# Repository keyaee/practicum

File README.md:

T06 - NES LockBox
=========

ECE411 - Practicum project

=======
Remember the Nintendo Entertainment System (NES)? We sure do.  This project is the brain child of Carlos Mariscal.  It simply is a box that locks. But thats not the cool part.  This box is electronically locked, and must be unlocked by using the old school NES controller as a user interface.  

YES! This thing rocks!!!

*[Visit the Wiki!](https://github.com/jalcok1/practicum/wiki)

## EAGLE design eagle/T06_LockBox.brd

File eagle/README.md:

This directory will hold needed Eagle .lib, .sch, and .brd
files necessary for the practicum project

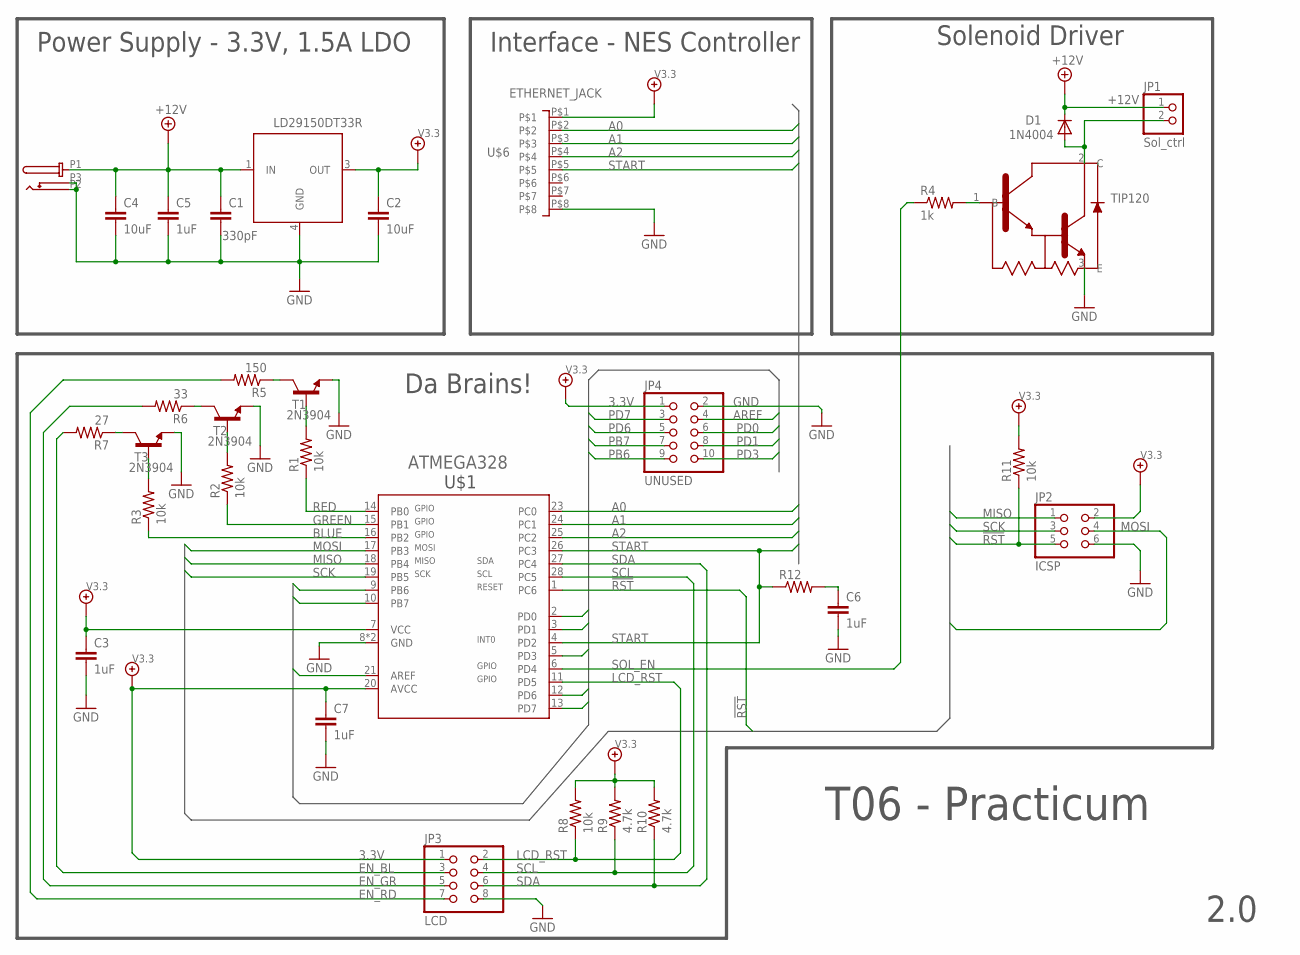
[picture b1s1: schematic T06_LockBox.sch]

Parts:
C1: 330pF; C0805
C2: 10uF; C0805
C3, C5, C6, C7: 1uF; C0805
C4: 10uF; C1206
D1: 1N4004; DO41-10
JP1: Sol_ctrl; 1X02
JP2: ICSP; 2X03
JP3: LCD; 2X04
JP4: UNUSED; 2X05
R1, R2, R3, R8: 10k; R0805
R4: 1k; M0805
R5: 150; R0805
R6: 33; R0805
R7: 27; R0805
R9, R10: 4.7k; R0805
R11: 10k; M0805
R12: R-US_M0805; M0805
T1, T2, T3: 2N3904; TO92-BCE
U$1: ATMEGA328; DIL28-3
U$2: LD29150DT33R; DPAK
U$3: PJ-102A
U$4: TIP120; T0220-3
U$6: ETHERNET_JACK; MODJACK8

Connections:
3.3V: C2.1, C3.1, C7.1, JP2.2, JP3.1, JP4.1, R8.2, R9.2, R10.2, R11.2, U$1.7 (VCC), U$1.20 (AVCC), U$2.3 (OUT), U$6.P$1
!RST: JP2.5, R11.1, U$1.1 (PC6)
+12V: C1.1, C4.1, C5.1, D1.C, JP1.1, U$2.1 (IN), U$3.P1 (PWR)
A0: U$1.23 (PC0), U$6.P$2
A1: U$1.24 (PC1), U$6.P$3
A2: U$1.25 (PC2), U$6.P$4
AREF: JP4.4, U$1.21 (AREF)
BLUE: R3.1, U$1.16 (PB2)
EN_BL: JP3.3, R7.2
EN_GR: JP3.5, R6.2
EN_RD: JP3.7, R5.2
GND: C1.2, C2.2, C3.2, C4.2, C5.2, C6.2, C7.2, JP2.6, JP3.8, JP4.2, T1.E, T2.E, T3.E, U$1.8 (GND), U$1.22 (GND), U$2.4 (GND), U$3.P2 (GND), U$3.P3 (GND), U$4.3 (E), U$6.P$8
GREEN: R2.1, U$1.15 (PB1)
LCD_RST: JP3.2, R8.1, U$1.11 (PD5)
MISO: JP2.1, U$1.18 (PB4)
MOSI: JP2.4, U$1.17 (PB3)
unnamed: R4.2, U$4.1 (B)
unnamed: C6.1, R12.2
unnamed: D1.A, JP1.2, U$4.2 (C)
unnamed: R1.2, T1.B
unnamed: R2.2, T2.B
unnamed: R3.2, T3.B
unnamed: R7.1, T3.C
unnamed: R6.1, T2.C
unnamed: R5.1, T1.C
PB6: JP4.9, U$1.9 (PB6)
PB7: JP4.7, U$1.10 (PB7)
PD0: JP4.6, U$1.2 (PD0)
PD1: JP4.8, U$1.3 (PD1)
PD3: JP4.10, U$1.5 (PD3)
PD6: JP4.5, U$1.12 (PD6)
PD7: JP4.3, U$1.13 (PD7)
RED: R1.1, U$1.14 (PB0)
SCK: JP2.3, U$1.19 (PB5)
SCL: JP3.4, R9.1, U$1.28 (PC5)
SDA: JP3.6, R10.1, U$1.27 (PC4)
SOL_EN: R4.1, U$1.6 (PD4)
START: R12.1, U$1.4 (PD2), U$1.26 (PC3), U$6.P$5

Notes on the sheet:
Power Supply - 3.3V, 1.5A LDO
Interface - NES Controller
Solenoid Driver
T06 - Practicum
2.0
Da Brains!

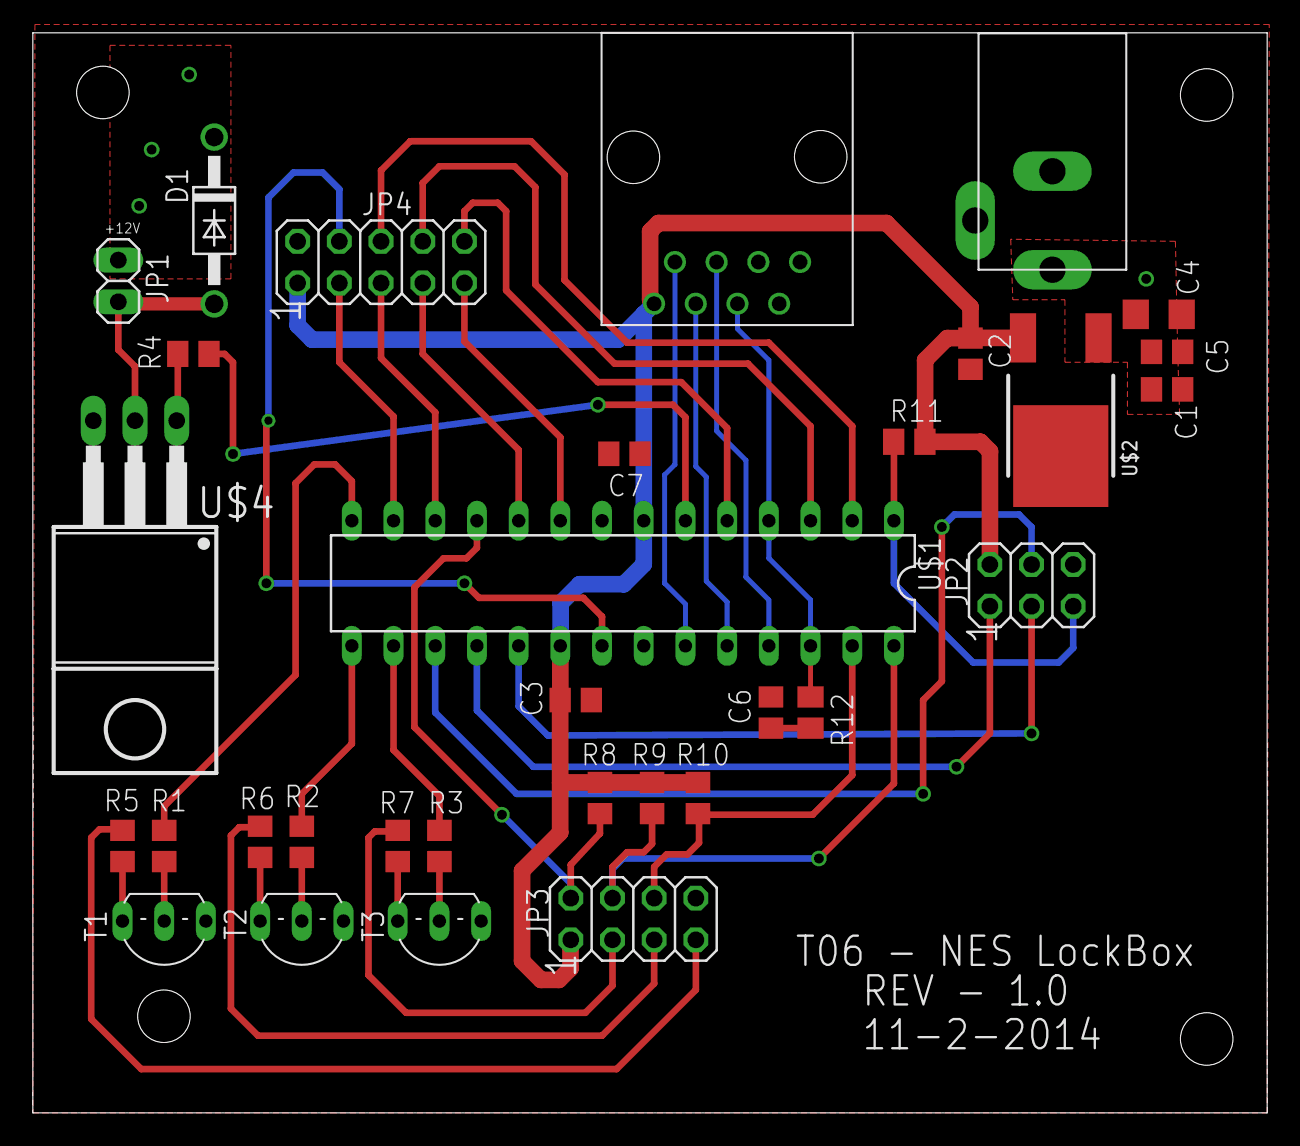
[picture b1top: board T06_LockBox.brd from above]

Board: 2 copper layers, 75.2 x 65.8 mm, 32 parts (0 on the bottom side), 38 nets.

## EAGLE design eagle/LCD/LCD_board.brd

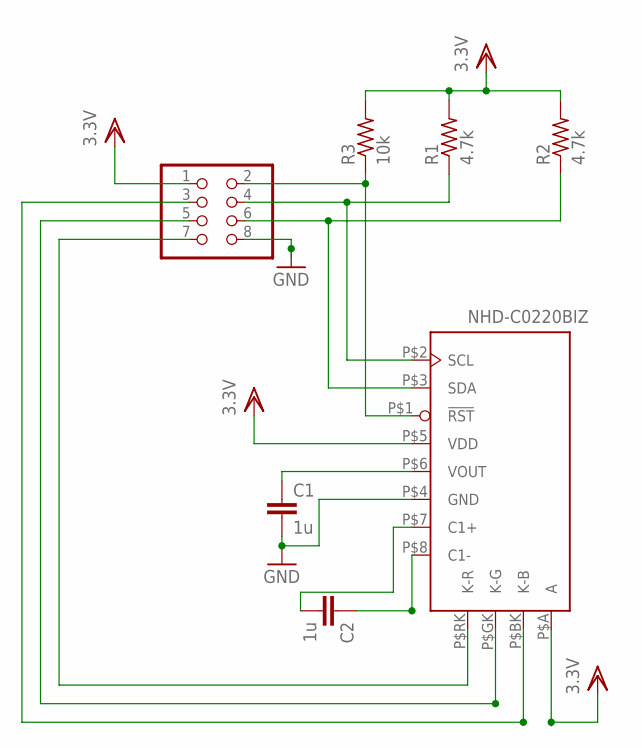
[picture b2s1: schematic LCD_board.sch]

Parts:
C1, C2: 1u; C0805
DATALINES: To MPU; 2X04
R1, R2: 4.7k; M0805
R3: 10k; M0805
U$1: NHD-C0220BIZ; NHD-C0220BIZ-LCD

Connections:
3.3V: DATALINES.1, R1.2, R2.2, R3.2, U$1.P$5 (VDD), U$1.P$A (A)
!LCD_RST: DATALINES.2, R3.1, U$1.P$1 (!RST)
C1+: C2.2, U$1.P$7 (C1+)
EN_BL: DATALINES.3, U$1.P$BK (K-B)
EN_G: DATALINES.5, U$1.P$GK (K-G)
EN_RD: DATALINES.7, U$1.P$RK (K-R)
GND: C1.2, DATALINES.8, U$1.P$4 (GND)
unnamed: C2.1, U$1.P$8 (C1-)
unnamed: C1.1, U$1.P$6 (VOUT)
SCL: DATALINES.4, R1.1, U$1.P$2 (SCL)
SDA: DATALINES.6, R2.1, U$1.P$3 (SDA)

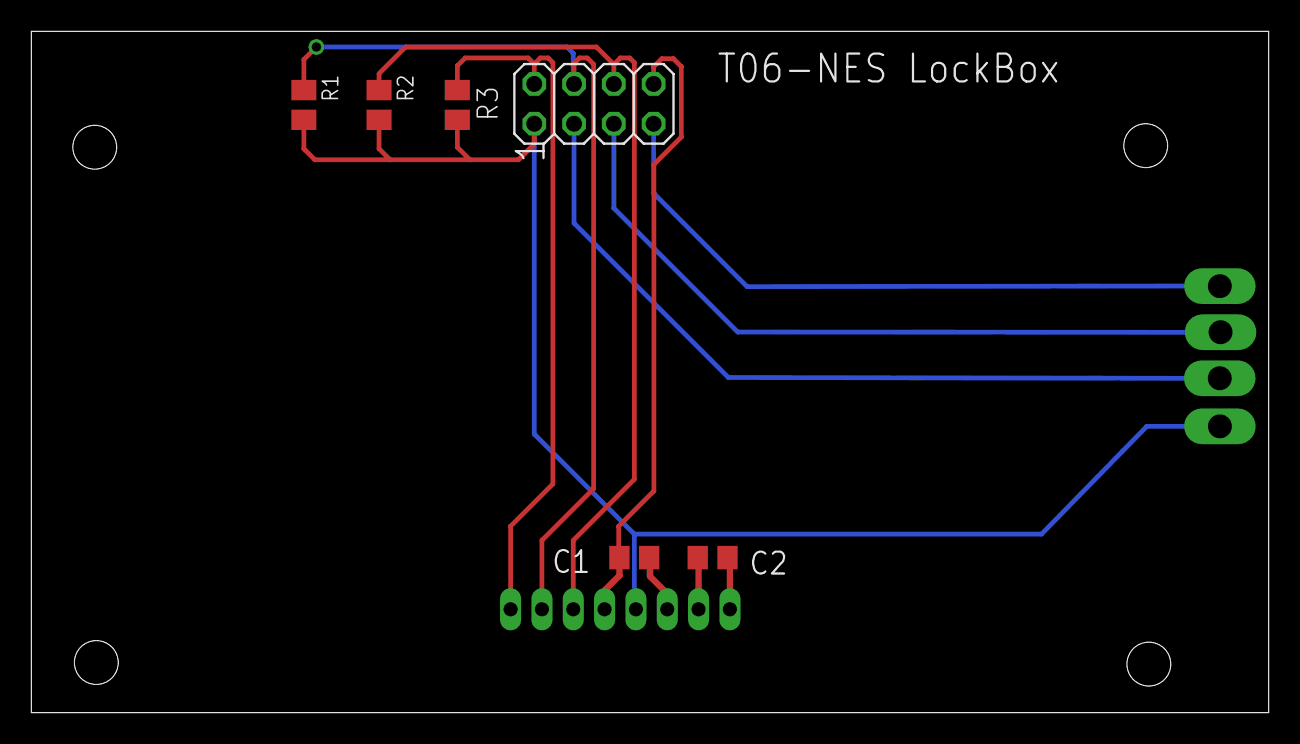
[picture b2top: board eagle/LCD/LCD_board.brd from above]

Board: 2 copper layers, 79.0 x 43.5 mm, 7 parts (1 on the bottom side), 11 nets.

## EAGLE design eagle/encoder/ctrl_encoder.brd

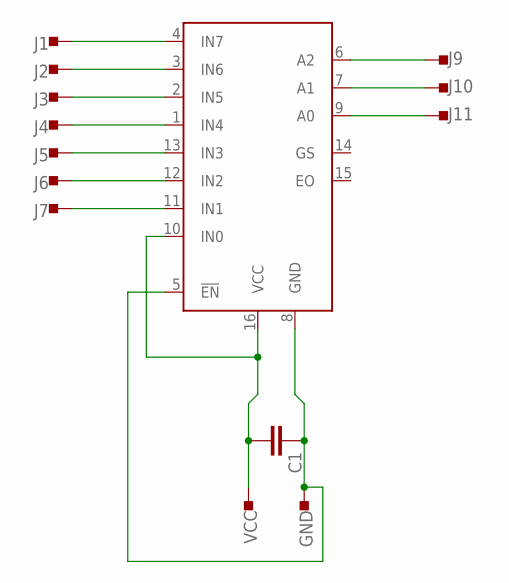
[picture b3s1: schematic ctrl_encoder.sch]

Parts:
C1: C; C0805
GND: PAD; TEST_PAD
J1, J2, J3, J4, J5, J6, J7, J9, J10, J11: PAD; TEST_PAD
U$1: SN74HC148DR; SO16
VCC: PAD; TEST_PAD

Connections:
GND: C1.1, GND.P$1, U$1.5 (!EN), U$1.8 (GND)
unnamed: C1.2, U$1.10 (IN0), U$1.16 (VCC), VCC.P$1
unnamed: J9.P$1, U$1.6 (A2)
unnamed: J1.P$1, U$1.4 (IN7)
unnamed: J2.P$1, U$1.3 (IN6)
unnamed: J3.P$1, U$1.2 (IN5)
unnamed: J4.P$1, U$1.1 (IN4)
unnamed: J5.P$1, U$1.13 (IN3)
unnamed: J6.P$1, U$1.12 (IN2)
unnamed: J7.P$1, U$1.11 (IN1)
unnamed: J10.P$1, U$1.7 (A1)
unnamed: J11.P$1, U$1.9 (A0)

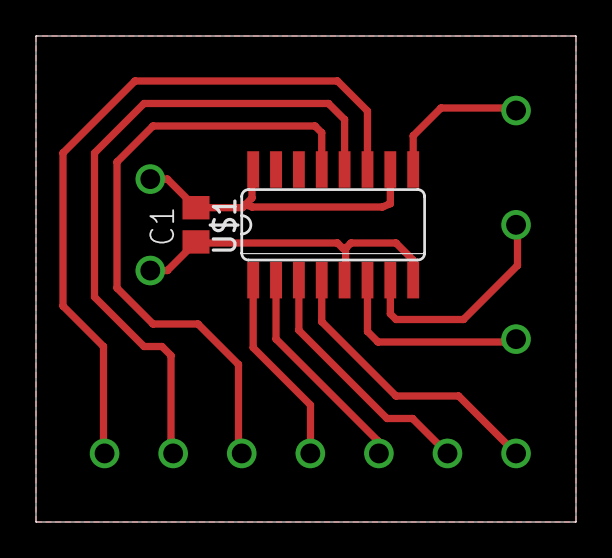
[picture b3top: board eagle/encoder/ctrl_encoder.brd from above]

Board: 2 copper layers, 30.0 x 27.0 mm, 14 parts (0 on the bottom side), 12 nets.

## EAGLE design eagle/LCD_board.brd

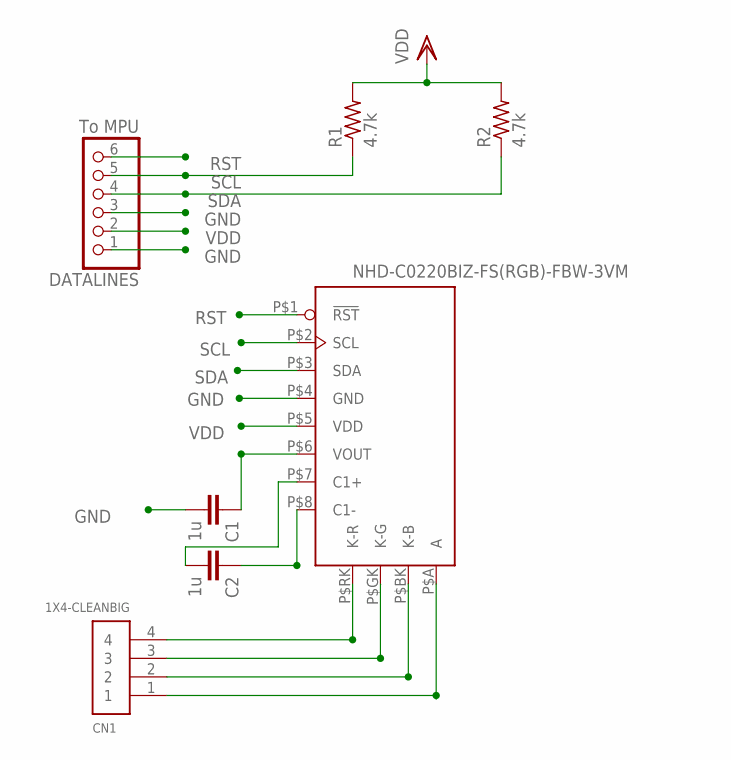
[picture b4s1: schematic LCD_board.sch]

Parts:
C1, C2: 1u; C15B8
CN1: 1X4-CLEANBIG; 1X04-CLEANBIG
DATALINES: To MPU; 1X06
R1, R2: 4.7k; 0204/5
U$1: NHD-C0220BIZ-FS(RGB)-FBW-3VM; NHD-C0220BIZ-LCD

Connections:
A: CN1.4, U$1.P$RK (K-R)
C1+: C2.2, U$1.P$7 (C1+)
GK: CN1.2, U$1.P$BK (K-B)
GND: C1.2, DATALINES.1, DATALINES.3, U$1.P$4 (GND)
unnamed: C2.1, U$1.P$8 (C1-)
unnamed: CN1.3, U$1.P$GK (K-G)
unnamed: C1.1, U$1.P$6 (VOUT)
unnamed: CN1.1, U$1.P$A (A)
RST: DATALINES.6, U$1.P$1 (!RST)
SCL: DATALINES.5, R1.1, U$1.P$2 (SCL)
SDA: DATALINES.4, R2.1, U$1.P$3 (SDA)
VDD: DATALINES.2, R1.2, R2.2, U$1.P$5 (VDD)

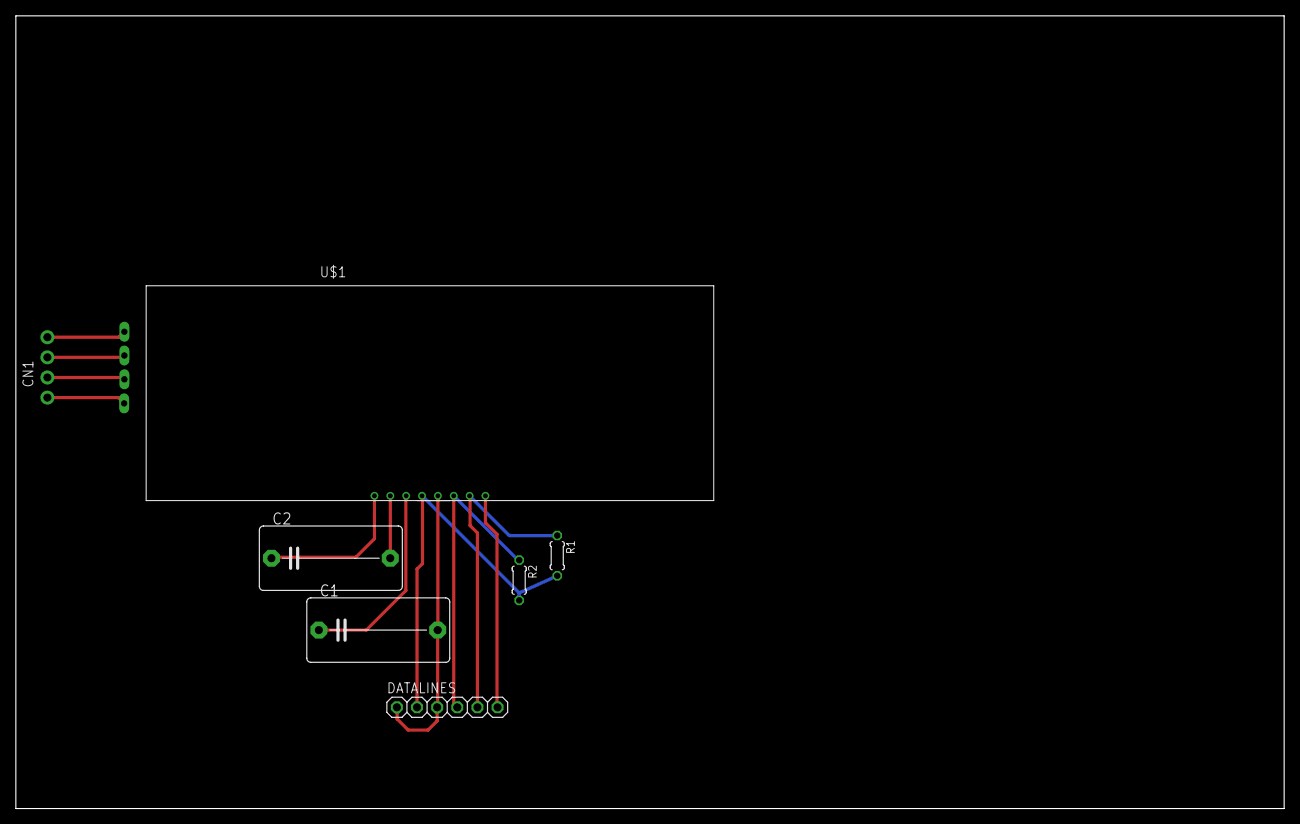
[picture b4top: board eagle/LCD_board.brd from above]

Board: 2 copper layers, 160.0 x 100.0 mm, 7 parts (0 on the bottom side), 12 nets.

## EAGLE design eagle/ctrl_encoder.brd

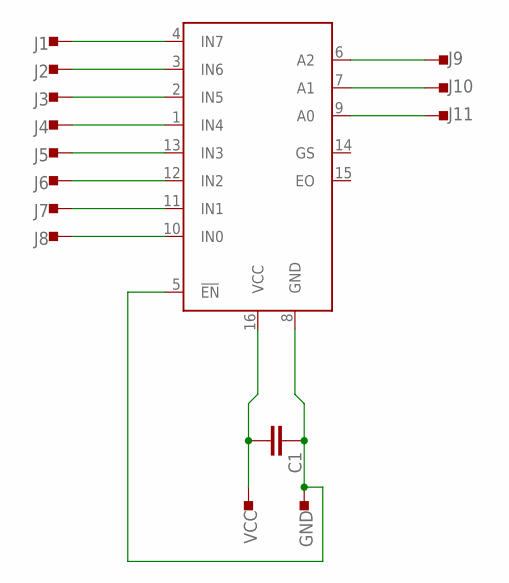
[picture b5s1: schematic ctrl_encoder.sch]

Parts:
C1: C; C0805
GND: PAD+SQUARE-1.5X1.5; PAD-1.5X1.5
J1, J2, J3, J4, J5, J6, J7, J8, J9, J10, J11: PAD+SQUARE-1.5X1.5; PAD-1.5X1.5
U$1: SN74HC148DR; SO16
VCC: PAD+SQUARE-1.5X1.5; PAD-1.5X1.5

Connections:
GND: C1.1, GND.PAD, U$1.5 (!EN), U$1.8 (GND)
unnamed: C1.2, U$1.16 (VCC), VCC.PAD
unnamed: J9.PAD, U$1.6 (A2)
unnamed: J1.PAD, U$1.4 (IN7)
unnamed: J2.PAD, U$1.3 (IN6)
unnamed: J3.PAD, U$1.2 (IN5)
unnamed: J4.PAD, U$1.1 (IN4)
unnamed: J5.PAD, U$1.13 (IN3)
unnamed: J6.PAD, U$1.12 (IN2)
unnamed: J7.PAD, U$1.11 (IN1)
unnamed: J8.PAD, U$1.10 (IN0)
unnamed: J10.PAD, U$1.7 (A1)
unnamed: J11.PAD, U$1.9 (A0)

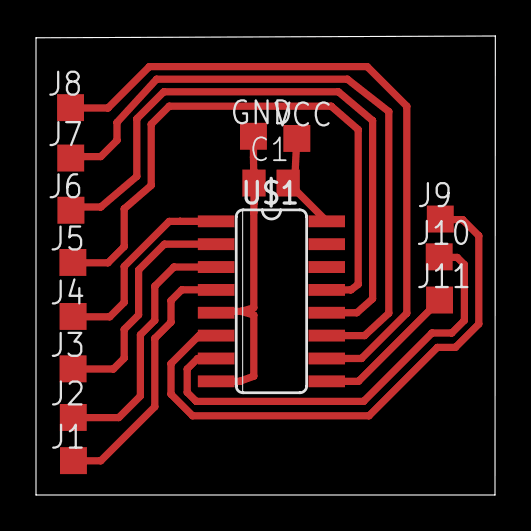
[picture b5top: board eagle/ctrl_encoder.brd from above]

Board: 2 copper layers, 25.5 x 25.5 mm, 15 parts (0 on the bottom side), 13 nets.

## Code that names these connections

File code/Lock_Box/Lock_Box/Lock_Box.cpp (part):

/*
this code is used to debug the NES controller interface,external interrupts, and timer interrupts.
LEDs are used for debug and are placed on pin B0-B3 with some resistors in series ~1kohm.
the input pins from the encoder are PC0-PC3 

I have started to write the main loop for the lock box I have incorporated the code that i had and have left 
to do comments through out the code. 
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an interrupt described above*/
ISR(TIMER1_COMPA_vect)
{
	//for debug-toggle LED on PB4++++++++++++++++++++++++++++++++++++++++++
	PORTB |= (1<<PORTB4); //turn blue LED on to signify we are in at home screen
	PORTB &= ~(1<<PORTB3); //turn red LED off
	//++++++++++++++++++++++++++++++++++++++++++
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
int main(void)
{
    //setting PBC0-PC3 as inputs
	DDRC &= ~((1<<DDC0)|(1<<DDC1)|(1<<DDC2)|(1<<DDC3));//all port B as inputs
	PORTC |= ((1<<PORTC0)|(1<<PORTC1)|(1<<PORTC2)|(1<<PORTC3));//enable pull-ups

	
	DDRB |= ((1<<DDB0)|(1<<DDB1)|(1<<DDB2)|(1<<DDB3)|(1<<DDB4)|(1<<DDB5)|(1<<DDB6)); //pin PB0-PB3 as outputs
	PORTB = 0x00;// all off
	 
	
	//configuring interrupt INT0
	DDRD &= ~(1<<DDD2); //PD2 as input
	PORTD |= (1<<PORTD2); //enable pull-up on PD2
	EICRA |= (1<<ISC01); //set interrupt on INT0 falling edge
	EIMSK |= (1<<INT0); //enable interrupt on INT0
	
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
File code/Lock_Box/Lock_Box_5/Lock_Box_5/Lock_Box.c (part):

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
int main(void)
{
    //setting PBC0-PC3 as inputs
	DDRC &= ~((1<<DDC0)|(1<<DDC1)|(1<<DDC2)|(1<<DDC3));//all port B as inputs
	PORTC |= ((1<<PORTC0)|(1<<PORTC1)|(1<<PORTC2)|(1<<PORTC3));//enable pull-ups
	
	DDRD |= ((1<<DDD5)|(1<<DDD4)); // setting PD5 and PD4 as output for solenoid and reset for LCD
	PORTD |= (1<<PORTD4); //set high for LCD reset (reset is active low)
	
	DDRB |= ((1<<DDB0)|(1<<DDB1)|(1<<DDB2)); //PB0-PB2 as outputs for LCD LEDs control
	
	LEDs(1,1,1); //all on -white

	
	
	//configuring interrupt INT0
	DDRD &= ~(1<<DDD2); //PD2 as input
	PORTD |= (1<<PORTD2); //enable pull-up on PD2
	EICRA |= (1<<ISC01); //set interrupt on INT0 falling edge
	EIMSK |= (1<<INT0); //enable interrupt on INT0
	
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
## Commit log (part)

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2014-10-02 Added eagle directory to the repo, this will hold all eagle associated files for the practicum project.
2014-10-02 Adding a datasheet directory
2014-10-03 This is to practice committing and syncing
2014-10-08 test changes
2014-10-08 Removing test changes to README.md
2014-10-08 testing app commit
    testing app commit
2014-10-08 atmega 328p data sheet
2014-10-08 adding parts with data sheets and supporting files
2014-10-08 block diagram of project
2014-10-08 moved the Atmel datasheet from datasheets directory to the parts/MCU directory to be consistant with the file system
2014-10-08 renamed spaces from block diagram jpg
2014-10-08 Added the controller interface jpeg to the ControllerMCUinterface.docx and modified naming conventions.
2014-10-08 new schematic for controller
2014-10-08 Testing commit for Luis
    added line to REDME.md
2014-10-09 adding some data sheets
2014-10-09 updates and adding a folder for invoices
2014-10-09 Started LockBox.lbr and added the ATMEGA328 symbol/footprint
2014-10-09 Minor formatting and puncuation changes.
2014-10-09 updating block diagram
2014-10-09 last project
    added the last project idea
2014-10-10 deleting copy
2014-10-10 Added LCD screen footprint and schematic to library
2014-10-11 adding some schematics and data sheets
2014-10-11 datasheets to datasheets folder
2014-10-11 naming files appropriately
2014-10-11 Small changes
2014-10-11 Added LDO schematic and footprint to LockBox.lbr
2014-10-11 Carlos data sheet mistake change
2014-10-11 deleting incorrect datasheets
2014-10-11 Added TIP120 Darlington Transistor footprint and schematic to Lockbox.lbr
2014-10-11 LCD board
    Jeff, I do have some issues
2014-10-12 Added S016 package to the 8:3 encoder
2014-10-12 Created footprint for the DC power jack
2014-10-12 Added symbol for the DC power jack to the LockBox.lbr
2014-10-12 Arduino pin out vs. atmega328
2014-10-12 cleaning up atmega328 folder
2014-10-13 Updating files
2014-10-13 Added names, changed presentation
2014-10-13 Deleted duplicate LCD_board.b#d and LCD_board.brd from eagle directory. Created a new LCD_board.brd file that no longer causes errors when trying to open it via eagle
2014-10-13 removed duplicate LCD_board.b#1 file from the repo
2014-10-13 DRC errors in the LCD_board.brd have been resolved. Traces have been routed and the board should be good to go.
2014-10-13 ethernet jack
    here u go jefe
2014-10-14 correction
2014-10-14 adding pinout
2014-10-16 created ctrl encoder board and schematic.
2014-10-16 minor change
2014-10-16 LCD board with pull up resistor
    This should give us a working screen with thru hole components just to
    check dimensions and use for debug. Next change resistor and capacitor
    for surface mount and determine if RGB resistors will be on this or the
    main board.
2014-10-16 Added gerber files folders
    The name are a redundant since the extension tells you what they are
    but I thought it was the easiest way for everybody to understand
2014-10-16 Added schematic frame to the library
2014-10-16 LCD Gerber files
    PSU formated Gerber files for LPKF
2014-10-17 Moved ctrl_encoder.dri file to GerberFiles/encoder Renamed Gerber\ files to GerberFiles
2014-10-17 More file management, added LCD folder and encoder folder and moved appropiate files.
2014-10-17 moved j1-j8 pins up on the ctrl_encoder.brd shrinking the actual size of the encoder board by several mm.
2014-10-18 blah blka
2014-10-18 controller driver
2014-10-18 updates
    added comments and some new variables.
2014-10-19 uptades
    added invoice for eBay
2014-10-19 invoice for ebay
2014-10-20 updates
    updated controller schematic
    added basic program flow
    updated pin out to MCU and encoder
2014-10-20 Added ground symbol to LockBox.lbr
2014-10-20 Modified the ATMEL chip schematic in LockBox.lbr, the schematic now updates properly when adding attributes to the port/pins in LockBox.sch.
2014-10-20 Finished the powersupply and LDO portion of the LockBox.sch, Added pwr/gnd and bypass cap to the ATMEL chip, updateded I2C pin attributes and added I2C bus.
2014-10-20 Added gnd and vout connections to the LCD screen in LockBox.sch Moved pins and modified part name in LockBox.lbr. These pins were poorly placed and were moved to allow for a cleaner schematic in Lock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
2014-10-20 Added KR, KG, KB, and A connections to the LCD screen.
2014-10-20 Updated LCD_board.sch with modified LCD screen schematic.
2014-10-20 LCD_board.brd is now a one layer board. Created new Gerber files and updated the GerberFiles/LCD directory with these new files
2014-10-20 updated ATMEL chip pin allocation.
2014-10-21 created folder for 411 class assignments
    we can put class assignments stuffs here
2014-10-21 Delete Microcontroller Tutorial - A Beginners Guide - YouTube.webloc
    will add a text file with link to youtube videos
2014-10-21 link to useful AVR tutorial
2014-10-21 Modified the symbol on the TIP120. The grid of the schematic was on an off scale making it difficult to make wire connections when using the part in the LockBox.sch.
2014-10-21 Added 0.6mm drill Test pad to LockBox.lbr
2014-10-21 Replaced surface mount pads with through hole pads. Added a polygon to the .brd and increased the size of the isolate from 10mil to 20mils, this should prevent solder from bridging to the remaining c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
2014-10-21 Removed previous gerber files and added new updated gerber files
2014-10-21 Ver2 Gerber files for encoder
    Per Carlos request created new Gerber files for encoder with thru hole.
2014-10-21 updates
    added some more bullet points
2014-10-21 program flow change
    SELECT button will cause interrupt only in first screen
2014-10-21 updating pin out
2014-10-21 datasheet for diode in parallel with solenoid
2014-10-21 Added 2pin header and 12V supply symbol to LockBox.lbr
2014-10-21 changed pin out
    had to change the pinout of the MCU because the outputs of the
    Controller are pull ups and one of the pins I was using was the same
    for the SPI bus which need to be free not pulled high or else
    programming would not be possible
2014-10-21 Added bus and related nets for LED color control on the LCD screen
2014-10-22 changes on pinout
2014-10-22 adding new Driver for controller
    this code contains an update for the controller driver and also
    includes examples on external interrupts and timer interrupts
2014-10-22 Increased the size of the test pad through hole from 0.6mm to 1.1mm
2014-10-22 Testing Keya's git push pull
2014-10-23 Added cool info the the REDME.md file. The info in this file is the first thing that is visable when opening our GITHUB home page.
2014-10-23 removed the README.md
2014-10-24 Lock Box code
    the code is mostly done. we only need to develop drivers for the LCD. I
    tried to comment most of the code I will continue to add comments ASAP.
2014-10-24 adding folder for images and videos
    we can use this folder to document our progress with images
2014-10-24 testing for size
2014-10-24 testing size
2014-10-24 updating images
2014-10-24 Update to assignment 3 document
2014-10-24 Others will need to contribute to this document
2014-10-25 edit to PDS
    IU made some edits to the PDS
2014-10-25 no changes...
    just my MAC being crazy
2014-10-25 Added team number to title page, added information for the cost and environmental categories, also made some small formatting changes.
2014-10-25 small edits
    did some editing on the document
2014-10-25 File management: I cleaned up the practicum directory
2014-10-25 Minor changes and suggestions
    Used track changes and comments to identify my ideas and make it easy
    to accept or reject. Made a few comments and observations to make
    marketing and engineering requirements a bit more different.
2014-10-26 file upkeeping
    deleted files that were associated with Atmel Studio. the code folder
    should only contain .ccp and .h files.
    * lock box code now can handle the user holding down a button without
    registering as an continuous input
2014-10-27 Finalized Luis' comments and corrections. Added some formatting changes. This Paper is ready for final review.
2014-10-27 minor edit
2014-10-27 Final review is done. No further work needed. :-)
2014-10-28 Added AVCC connection to VCC on the ATMEL chip. Added document number.
2014-10-30 LCD RGB has the modified width
    Change the hole width of the RGB pinto fit the pins. I hope…
2014-10-30 adjusted hight
    after hole size adjustment hight was a bit off and readjusted to match
    data sheet
2014-10-30 adding some files
    added images for controller prototype, ethernet pin out, edits on
    encoder schmeatic
2014-10-30 Updates
    made changes to encoder schematic. changed the SELECT button for the
    START button. instead of pressing SELECT to begin it is now the START
    button
2014-10-31 Added 2x3 header component for ATMEL chip programming to the LockBox.lbr. Also made small changes to bus's on the LockBox.sch
2014-10-31 Added 6pin 2x3 headder to the Lockbox.sch. Routed necessary nets associated with programing the ATMEL chip. A switch will need to be added for the RESET. This schematic version is 1.1.
2014-10-31 Moved EN_RD from PB1 to PB0 and EN_GR from PB0 to PB1, this change was necessary to aid in board layout
2014-10-31 Started LockBox.brd layout
2014-10-31 Finished first draft of board layout. I have not ran a DRU yet because I dont have the OSHPARK DRU files.
2014-11-01 testing braching
2014-11-01 Added 1N3904 transistor to the library
2014-11-01 Added transister pulldown network for LCD-LED backlighting
2014-11-01 Renamed eagle files to include group name as per Andrews request
2014-11-02 Added connections to unused pins on the schematic. Finished routing wires to the unused pin header locaton on the board.
2014-11-02 Adding 2N3904 datasheet
2014-11-02 Increased the drill size of the 8 inline pins on the LDC screen. The size went from 0.6mm ---> 0.8mm. This should provide plenty of room and the LCD screen should just fit
2014-11-02 Working but still alpha code fro LCD
    Initial LCD code Timing issues resolved. Good enough for testing user
    inputs.
    Still needs print fiction (ability to send strings) sf better
    comments.
2014-11-03 Replaced 10uF 25V 0805 cap with 1206 cap. 0805 package size with those values is not available.
    Moved the tplace labels of all components on the .brd
2014-11-03 spell checker
2014-11-03 Added 2x5 pin headder and pull up resistor to the ATMEGA reset line.
2014-11-04 Added DigiKey Invoice
2014-11-04 Replaced incorrect power jack with correct power jack datasheet
2014-11-04 Increased drill size from .76mm to .9mm on the ethernet jack, this should provide enough space for pin diameter variations.
2014-11-04 Meeting minutes
    Added folder to include meeting minutes and added minutes from today.
2014-11-04 changed extension
2014-11-05 renamed folder
2014-11-06 8 LDC round pads to long pads and increased diameter of the drills.
2014-11-06 small chagnes
2014-11-06 Updated LCD board with surface mount components and a 2x4 header connector
2014-11-07 Created 2 layer LDC board with smaller footprint than previous versions
2014-11-07 Added drill holes to the LCD screen that are necessary for hardware mounting
2014-11-07 found one connection not routed. fixed the connection and all better :-)
2014-11-07 Removed code
    code would not run without the “solution” file
2014-11-08 Added Schedule/Gannt Chart to Assignments folder
2014-11-08 Box
    just did a first box design and planing on laser cutting before next
    Friday where we can begin trouble shooting or making suggestions for
    final design.
2014-11-09 expenses
    forgot to add LCD invoice
2014-11-09 Added Gannt chart to 411_assignments
2014-11-09 edits to invoices
    added an invoice from digikey.
2014-11-10 new images
2014-11-11 Added my expenses to the expenses_Paid.xlsx
